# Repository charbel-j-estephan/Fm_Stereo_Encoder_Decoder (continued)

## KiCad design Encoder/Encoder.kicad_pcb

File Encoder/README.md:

# FM Stereo Encoder

## Final version

The final version is Encoder. Open Encoder.kicad_pro in KiCad 10. It holds the schematic (Encoder.kicad_sch) and the board (Encoder.kicad_pcb). Use these two files for printing and for building.

## Goal of this part

This board is the encoder half of the FM stereo project. It takes the left and right audio from the J3 input and turns them into one stereo multiplex (MPX) signal on the J4 output. The output feeds the FM transmitter module.

The board does these jobs.

1. It protects the inputs and filters the audio to 15 kHz.
2. It builds the sum (left plus right) and the difference (left minus right).
3. It makes a 38 kHz carrier. A CD4046 phase locked loop locks to a 19 kHz sine you feed into the 2 pin screw terminal (J5) and doubles it.
4. It modulates the difference signal onto the 38 kHz carrier with an MC1496.
5. It adds the sum, the modulated difference and the 19 kHz pilot into one MPX signal and filters it.

JP1 flips the carrier phase. If left and right come out swapped at the receiver, move the JP1 shunt to the other position. No reprint is needed.

## Board rules

- Tracks are 0.5 mm. The plus and minus 9 V rails use 0.8 mm tracks.
- Vias are 1.6 mm with a 0.8 mm drill. This is the board sent to PCBWay on Oct 24 (the "bigger vias" Gerbers).
- The four corner holes are 3.2 mm for M3 screws.
- Test points are single male header pins with 2.54 mm pitch. Break them off a 40 pin strip.
- The board is about 149 by 150 mm.

## Other files in this folder

- FM_Encoder_Build_and_Test_Guide.pdf is the stage by stage soldering and test guide. Follow it in order.
- FM_Encoder_Buy_List.xlsx is the EKT buy list with links and prices.
- MC1496.kicad_sym and R0.kicad_sym are symbol libraries the project needs. Do not delete them.

## Known open points

- J5 is a 2 pin 5.08 mm screw terminal. Pin 1 is the signal and pin 2 is ground. Feed it from a female BNC screw junction (EKT 426959) fixed to a bracket beside the board. The center screw goes to pin 1 and the shield screw goes to pin 2. No BNC part sits on the board.
- R51 (12k) and C47 (1n) set the VCO range. Check the free running frequency on TP33 during stage 7 of the guide.
- EKT does not stock 360k, 2.4k and 1.2n. The guide shows the substitutes.

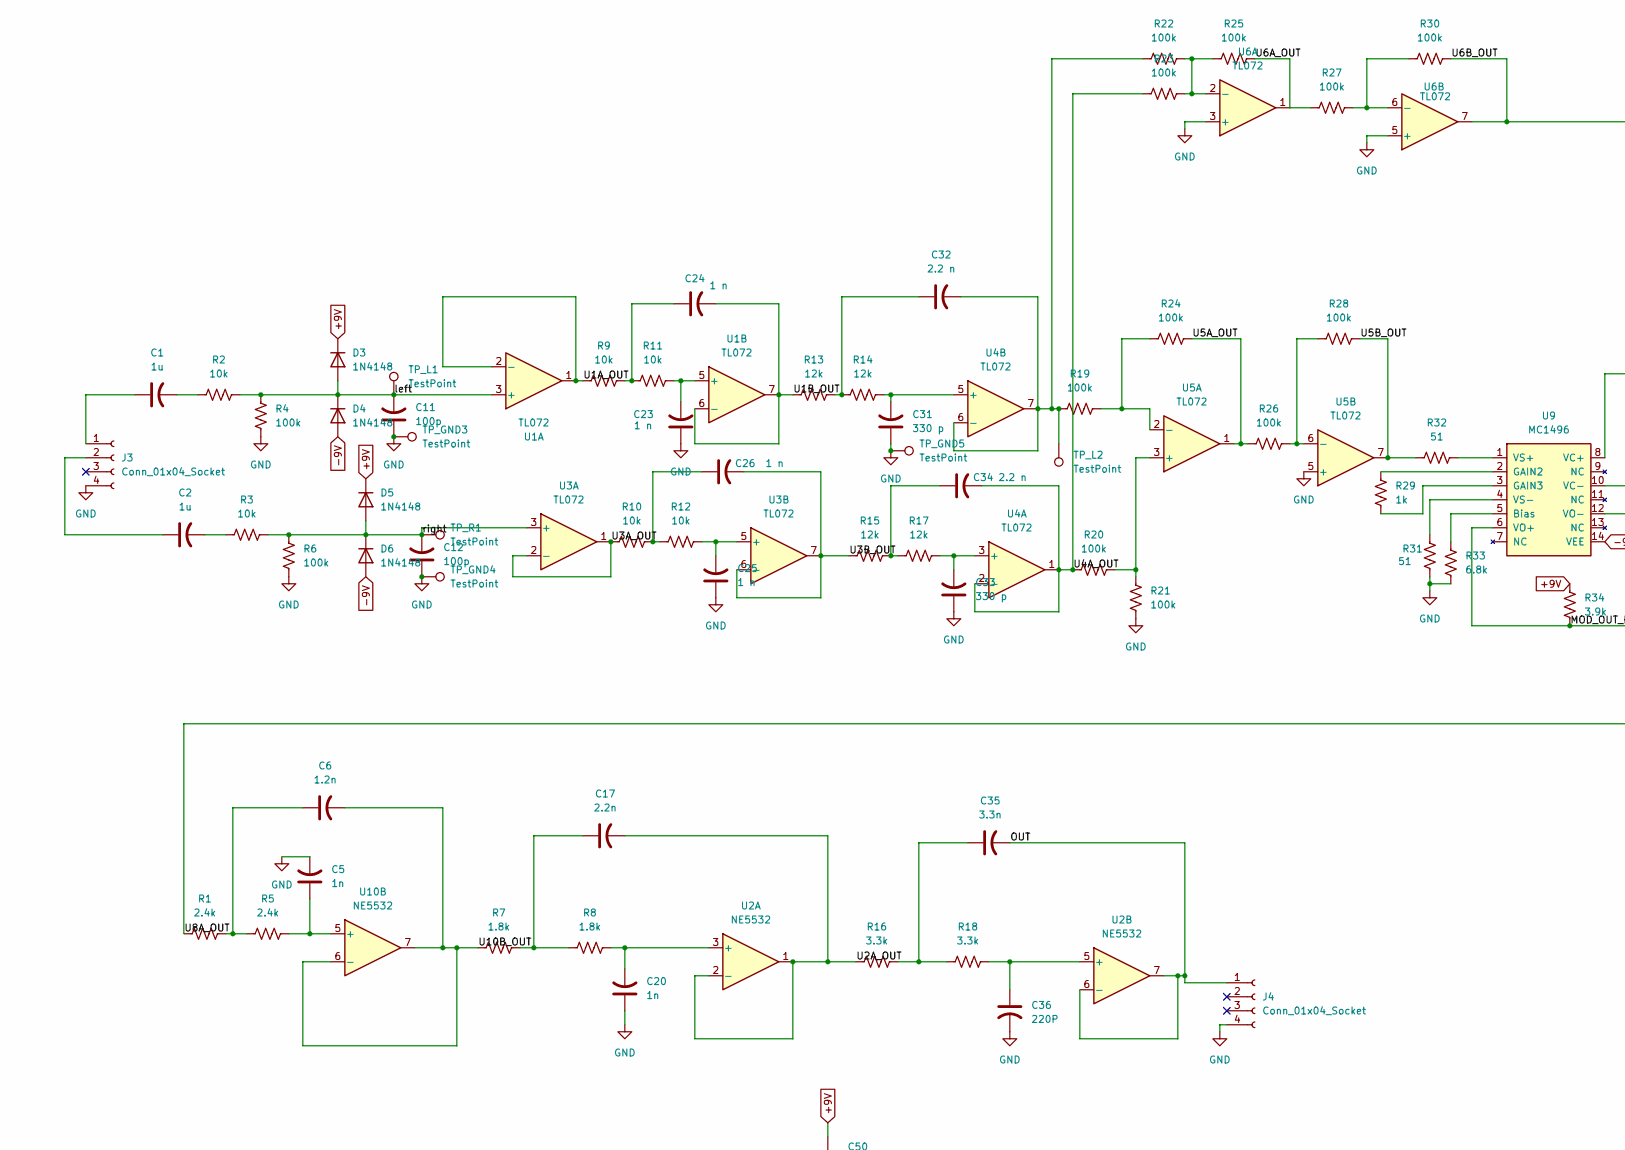
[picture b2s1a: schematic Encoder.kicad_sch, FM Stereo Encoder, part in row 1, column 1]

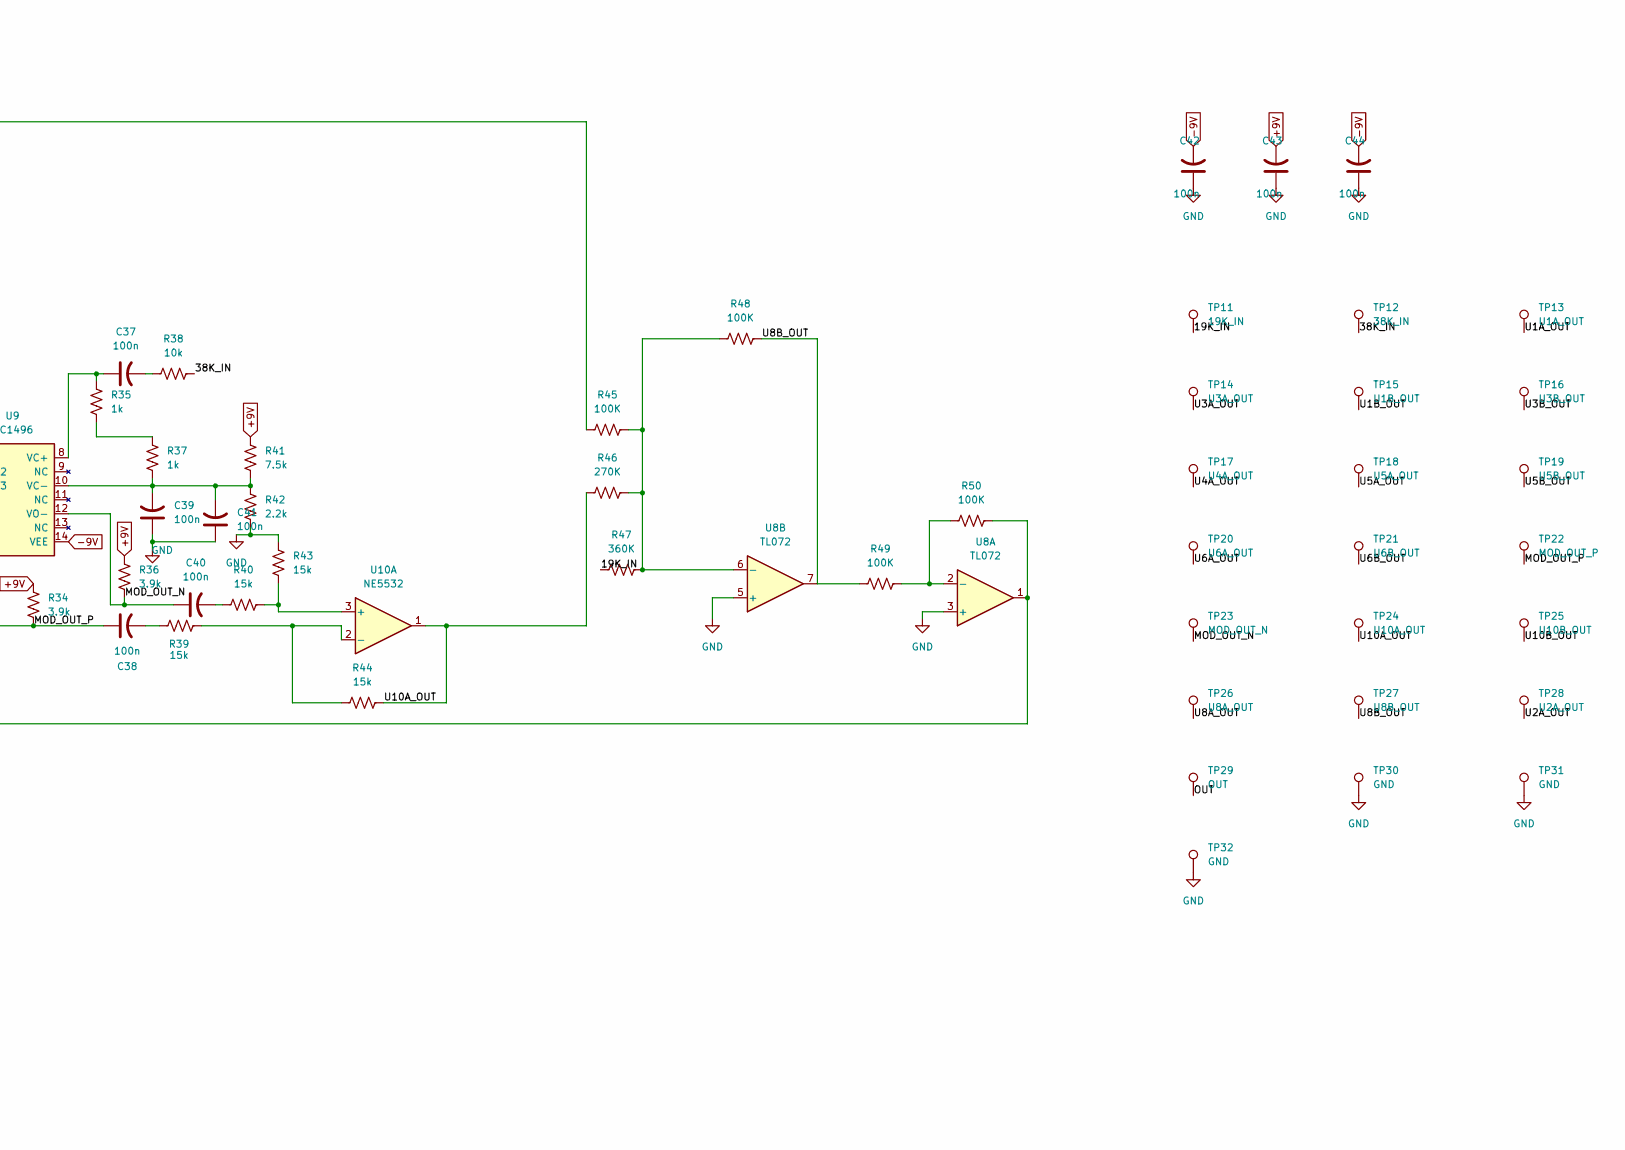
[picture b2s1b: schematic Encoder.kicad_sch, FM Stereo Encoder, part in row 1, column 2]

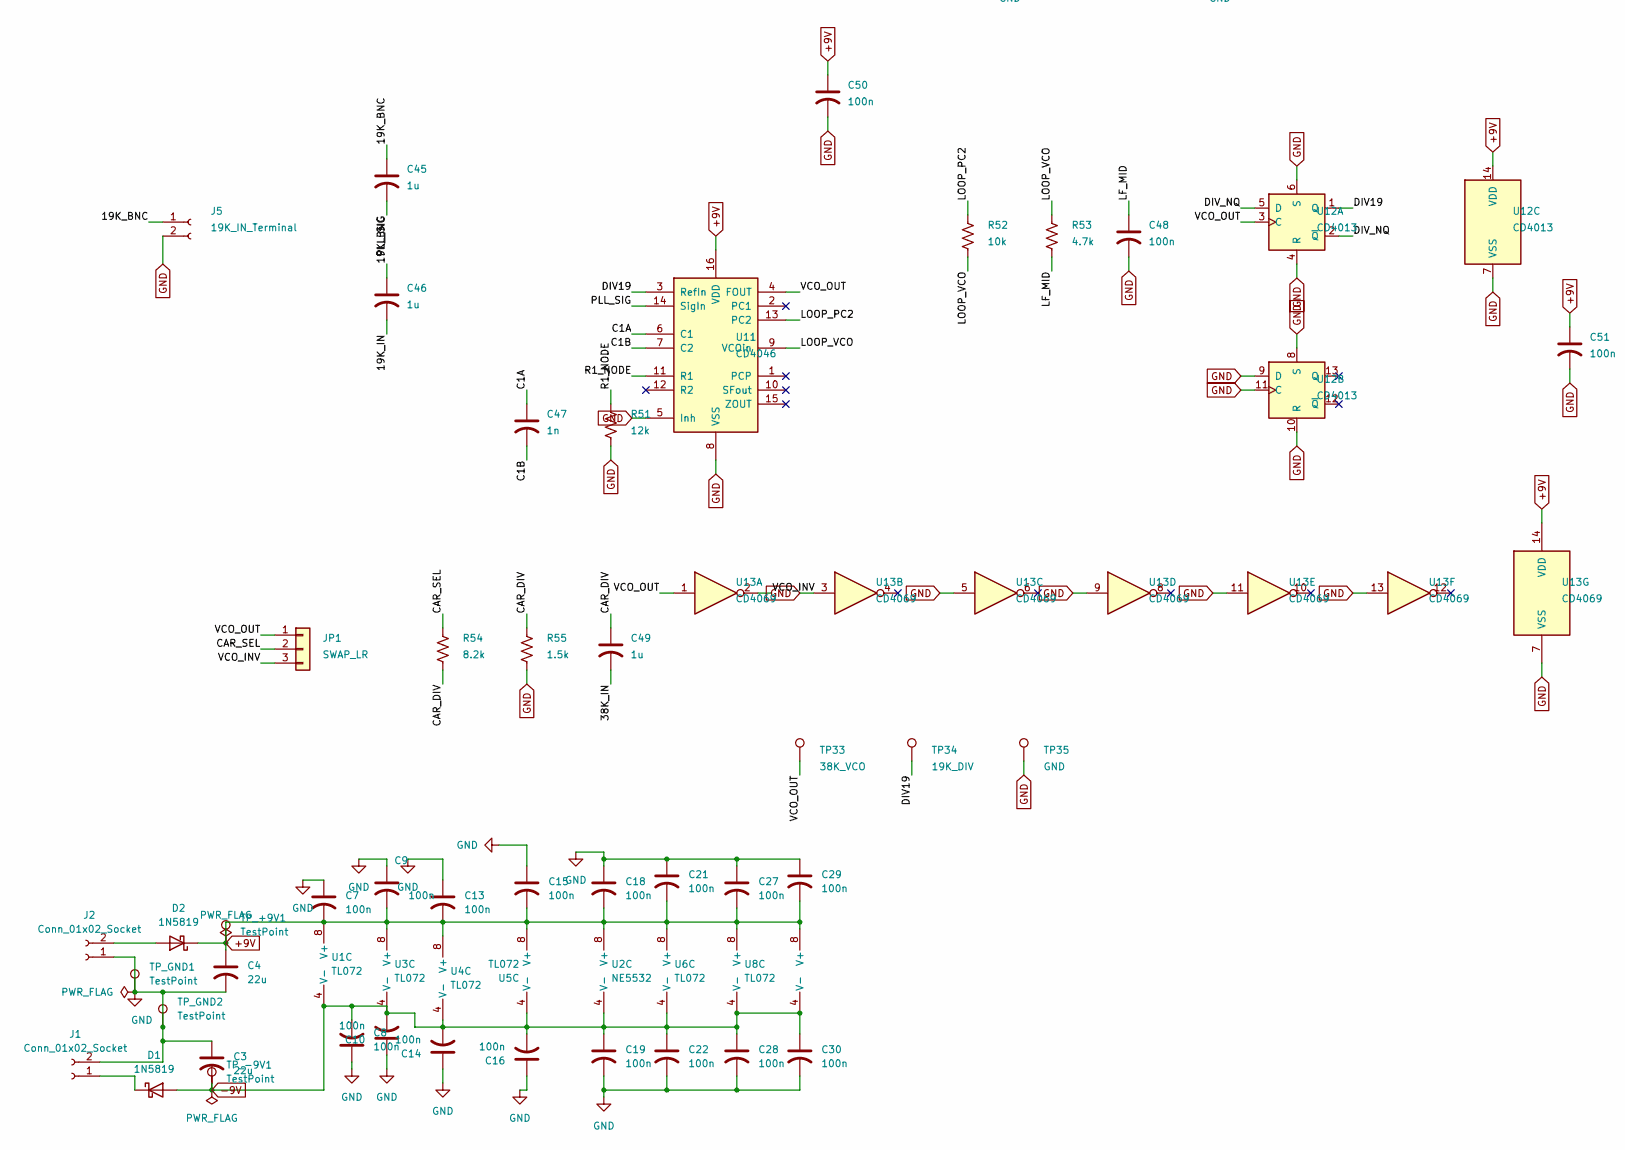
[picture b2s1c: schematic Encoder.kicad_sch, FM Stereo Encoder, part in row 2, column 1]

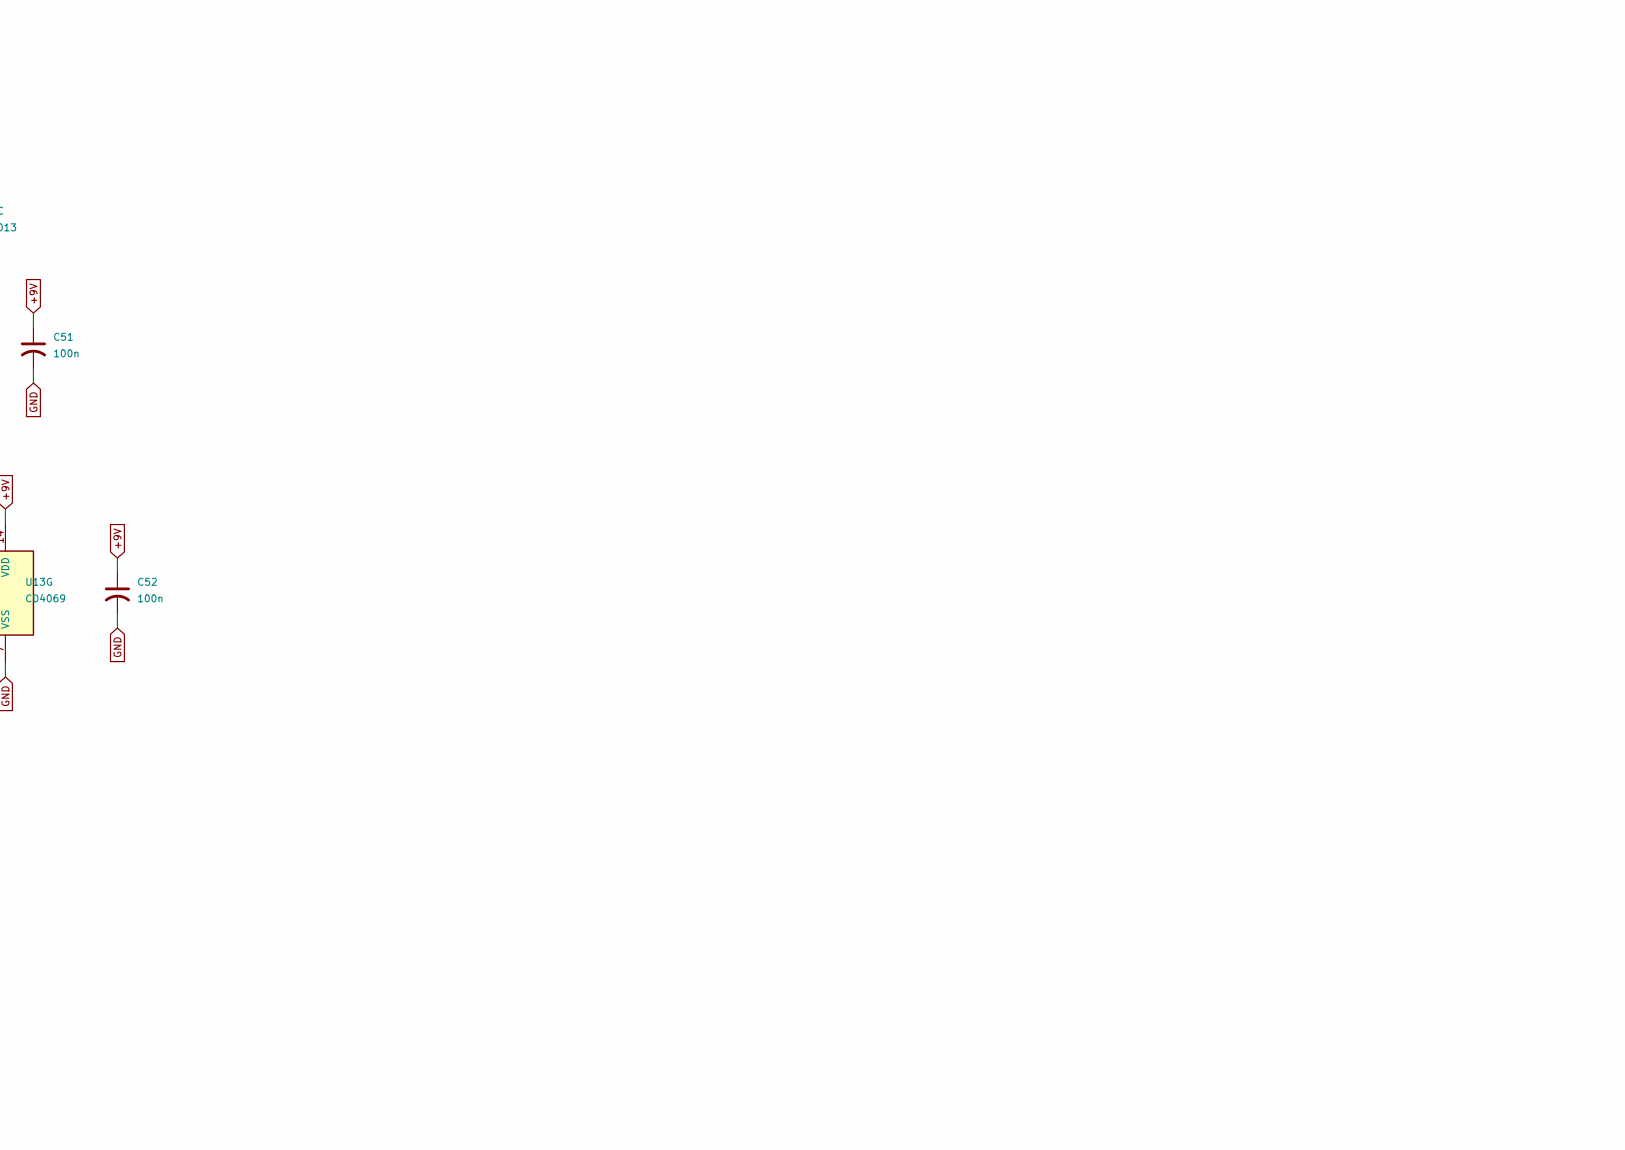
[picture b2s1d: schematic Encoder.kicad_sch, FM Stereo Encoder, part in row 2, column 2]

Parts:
C1, C2, C45, C46, C49: 1u; C_Rect_L7.2mm_W3.5mm_P5.00mm
C3, C4: 22u; CP_Radial_D8.0mm_P3.50mm
C5, C20, C47: 1n; C_Disc_D5.0mm_W2.5mm_P5.00mm
C6: 1.2n; C_Disc_D5.0mm_W2.5mm_P5.00mm
C7, C8, C9, C10, C13, C14, C15, C16, C18, C19, C21, C22, C27, C28, C29, C30, C37, C38, C39, C40, C41, C42, C43, C44, C48, C50, C51, C52: 100n; C_Disc_D5.0mm_W2.5mm_P5.00mm
C11, C12: 100p; C_Disc_D3.0mm_W2.0mm_P2.50mm
C17: 2.2n; C_Disc_D5.0mm_W2.5mm_P5.00mm
C23, C24, C25, C26: 1 n; C_Disc_D5.0mm_W2.5mm_P5.00mm
C31, C33: 330 p; C_Disc_D5.0mm_W2.5mm_P5.00mm
C32, C34: 2.2 n; C_Disc_D5.0mm_W2.5mm_P5.00mm
C35: 3.3n; C_Disc_D5.0mm_W2.5mm_P5.00mm
C36: 220P; C_Disc_D5.0mm_W2.5mm_P5.00mm
D1, D2: 1N5819; D_DO-41_SOD81_P10.16mm_Horizontal
D3, D4, D5, D6: 1N4148; D_DO-35_SOD27_P7.62mm_Horizontal
J1, J2: Conn_01x02_Socket; TerminalBlock_Phoenix_MKDS-1,5-2-5.08_1x02_P5.08mm_Horizont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
J3, J4: Conn_01x04_Socket; PinSocket_1x04_P2.54mm_Vertical
J5: 19K_IN_Terminal; TerminalBlock_Phoenix_MKDS-1,5-2-5.08_1x02_P5.08mm_Horizont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
JP1: SWAP_LR; PinHeader_1x03_P2.54mm_Vertical
R1, R5: 2.4k; R_Axial_DIN0207_L6.3mm_D2.5mm_P10.16mm_Horizontal
R2, R3, R9, R10, R11, R12, R38, R52: 10k; R_Axial_DIN0207_L6.3mm_D2.5mm_P10.16mm_Horizontal
R4, R6, R19, R20, R21, R22, R23, R24, R25, R26, R27, R28, R30: 100k; R_Axial_DIN0207_L6.3mm_D2.5mm_P10.16mm_Horizontal
R7, R8: 1.8k; R_Axial_DIN0207_L6.3mm_D2.5mm_P10.16mm_Horizontal
R13, R14, R15, R17, R51: 12k; R_Axial_DIN0207_L6.3mm_D2.5mm_P10.16mm_Horizontal
R16, R18: 3.3k; R_Axial_DIN0207_L6.3mm_D2.5mm_P10.16mm_Horizontal
R29, R35, R37: 1k; R_Axial_DIN0207_L6.3mm_D2.5mm_P10.16mm_Horizontal
R31, R32: 51; R_Axial_DIN0207_L6.3mm_D2.5mm_P10.16mm_Horizontal
R33: 6.8k; R_Axial_DIN0207_L6.3mm_D2.5mm_P10.16mm_Horizontal
R34, R36: 3.9k; R_Axial_DIN0207_L6.3mm_D2.5mm_P10.16mm_Horizontal
R39, R40, R43, R44: 15k; R_Axial_DIN0207_L6.3mm_D2.5mm_P10.16mm_Horizontal
R41: 7.5k; R_Axial_DIN0207_L6.3mm_D2.5mm_P10.16mm_Horizontal
R42: 2.2k; R_Axial_DIN0207_L6.3mm_D2.5mm_P10.16mm_Horizontal
R45, R48, R49, R50: 100K; R_Axial_DIN0207_L6.3mm_D2.5mm_P10.16mm_Horizontal
R46: 270K; R_Axial_DIN0207_L6.3mm_D2.5mm_P10.16mm_Horizontal
R47: 360K; R_Axial_DIN0207_L6.3mm_D2.5mm_P10.16mm_Horizontal
R53: 4.7k; R_Axial_DIN0207_L6.3mm_D2.5mm_P10.16mm_Horizontal
R54: 8.2k; R_Axial_DIN0207_L6.3mm_D2.5mm_P10.16mm_Horizontal
R55: 1.5k; R_Axial_DIN0207_L6.3mm_D2.5mm_P10.16mm_Horizontal
TP11: 19K_IN; PinHeader_1x01_P2.54mm_Vertical
TP12: 38K_IN; PinHeader_1x01_P2.54mm_Vertical
TP13: U1A_OUT; PinHeader_1x01_P2.54mm_Vertical
TP14: U3A_OUT; PinHeader_1x01_P2.54mm_Vertical
TP15: U1B_OUT; PinHeader_1x01_P2.54mm_Vertical
TP16: U3B_OUT; PinHeader_1x01_P2.54mm_Vertical
TP17: U4A_OUT; PinHeader_1x01_P2.54mm_Vertical
TP18: U5A_OUT; PinHeader_1x01_P2.54mm_Vertical
TP19: U5B_OUT; PinHeader_1x01_P2.54mm_Vertical
TP20: U6A_OUT; PinHeader_1x01_P2.54mm_Vertical
TP21: U6B_OUT; PinHeader_1x01_P2.54mm_Vertical
TP22: MOD_OUT_P; PinHeader_1x01_P2.54mm_Vertical
TP23: MOD_OUT_N; PinHeader_1x01_P2.54mm_Vertical
TP24: U10A_OUT; PinHeader_1x01_P2.54mm_Vertical
TP25: U10B_OUT; PinHeader_1x01_P2.54mm_Vertical
TP26: U8A_OUT; PinHeader_1x01_P2.54mm_Vertical
TP27: U8B_OUT; PinHeader_1x01_P2.54mm_Vertical
TP28: U2A_OUT; PinHeader_1x01_P2.54mm_Vertical
TP29: OUT; PinHeader_1x01_P2.54mm_Vertical
TP30, TP31, TP32, TP35: GND; PinHeader_1x01_P2.54mm_Vertical
TP33: 38K_VCO; PinHeader_1x01_P2.54mm_Vertical
TP34: 19K_DIV; PinHeader_1x01_P2.54mm_Vertical
TP_+9V1: TestPoint; PinHeader_1x01_P2.54mm_Vertical
TP_-9V1: TestPoint; PinHeader_1x01_P2.54mm_Vertical
TP_GND1, TP_GND2, TP_GND3, TP_GND4, TP_GND5: TestPoint; PinHeader_1x01_P2.54mm_Vertical
TP_L1, TP_L2: TestPoint; PinHeader_1x01_P2.54mm_Vertical
TP_R1: TestPoint; PinHeader_1x01_P2.54mm_Vertical
U1, U3, U4, U5, U6, U8: TL072; DIP-8_W7.62mm_Socket
U2, U10: NE5532; DIP-8_W7.62mm_Socket
U9: MC1496; DIP-14_W7.62mm_Socket
U11: CD4046; DIP-16_W7.62mm_Socket
U12: CD4013; DIP-14_W7.62mm_Socket
U13: CD4069; DIP-14_W7.62mm_Socket

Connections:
+9V: C4.1, C7.2, C9.2, C13.2, C15.2, C18.2, C21.2, C27.2, C29.2, C43.2, C50.1, C51.1, C52.1, D2.1 (K), D3.1 (K), D5.1 (K), R34.1, R36.1, R41.1, TP_+9V1.1, U1.8 (V+), U2.8 (V+), U3.8 (V+), U4.8 (V+), U5.8 (V+), U6.8 (V+), U8.8 (V+), U10.8 (V+), U11.16 (VDD), U12.14 (VDD), U13.14 (VDD)
-9V: C3.2, C8.2, C10.2, C14.2, C16.2, C19.1, C22.1, C28.1, C30.1, C42.2, C44.2, D1.2 (A), D4.2 (A), D6.2 (A), TP_-9V1.1, U1.4 (V-), U2.4 (V-), U3.4 (V-), U4.4 (V-), U5.4 (V-), U6.4 (V-), U8.4 (V-), U9.14 (VEE), U10.4 (V-)
/19K_BNC: C45.1, C46.1, J5.1
/19K_IN: C46.2, R47.1, TP11.1
/38K_IN: C49.2, R38.2, TP12.1
/C1A: C47.1, U11.6 (C1)
/C1B: C47.2, U11.7 (C2)
/CAR_DIV: C49.1, R54.2, R55.1
/CAR_SEL: JP1.2, R54.1
/DIV19: TP34.1, U11.3 (RefIn), U12.1 (Q)
/DIV_NQ: U12.2 (~Q), U12.5 (D)
/LF_MID: C48.1, R53.2
/LOOP_PC2: R52.1, U11.13 (PC2)
/LOOP_VCO: R52.2, R53.1, U11.9 (VCOin)
/MOD_OUT_N: C40.1, R36.2, TP23.1, U9.12 (VO-)
/MOD_OUT_P: C38.1, R34.2, TP22.1, U9.6 (VO+)
/OUT: C35.2, J4.1, TP29.1, U2.6 (-), U2.7
/PLL_SIG: C45.2, U11.14 (SigIn)
/R1_NODE: R51.1, U11.11 (R1)
/U1A_OUT: R9.1, TP13.1, U1.1, U1.2 (-)
/U1B_OUT: C24.2, R13.1, TP15.1, U1.6 (-), U1.7
/U2A_OUT: C17.2, R16.1, TP28.1, U2.1, U2.2 (-)
/U3A_OUT: R10.1, TP14.1, U3.1, U3.2 (-)
/U3B_OUT: C26.2, R15.1, TP16.1, U3.6 (-), U3.7
/U4A_OUT: C34.2, R20.1, R23.1, TP17.1, U4.1, U4.2 (-)
/U5A_OUT: R24.2, R26.1, TP18.1, U5.1
/U5B_OUT: R28.2, R32.1, TP19.1, U5.7
/U6A_OUT: R25.2, R27.1, TP20.1, U6.1
/U6B_OUT: R30.2, R45.1, TP21.1, U6.7
/U8A_OUT: R1.1, R50.2, TP26.1, U8.1
/U8B_OUT: R48.2, R49.1, TP27.1, U8.7
/U10A_OUT: R44.2, R46.1, TP24.1, U10.1
/U10B_OUT: C6.2, R7.1, TP25.1, U10.6 (-), U10.7
/VCO_INV: JP1.3, U13.2
/VCO_OUT: JP1.1, TP33.1, U11.4 (FOUT), U12.3 (C), U13.1
/left: C11.2, D3.2 (A), D4.1 (K), R2.2, R4.1, TP_L1.1, U1.3 (+)
/right: C12.2, D5.2 (A), D6.1 (K), R3.2, R6.1, TP_R1.1, U3.3 (+)
GND: C3.1, C4.2, C5.2, C7.1, C8.1, C9.1, C10.1, C11.1, C12.1, C13.1, C14.1, C15.1, C16.1, C18.1, C19.2, C20.1, C21.1, C22.2, C23.1, C25.1, C27.1, C28.2, C29.1, C30.2, C31.1, C33.1, C36.2, C39.1, C41.1, C42.1, C43.1, C44.1, C48.2, C50.2, C51.2, C52.2, J1.2, J2.1, J3.4, J4.4, J5.2, R4.2, R6.2, R21.2, R31.2, R33.2, R42.2, R43.1, R51.2, R55.2, TP30.1, TP31.1, TP32.1, TP35.1, TP_GND1.1, TP_GND2.1, TP_GND3.1, TP_GND4.1, TP_GND5.1, U5.5 (+), U6.3 (+), U6.5 (+), U8.3 (+), U8.5 (+), U11.5 (Inh), U11.8 (VSS), U12.4 (R), U12.6 (S), U12.7 (VSS), U12.8 (S), U12.9 (D), U12.10 (R), U12.11 (C), U13.3, U13.5, U13.7 (VSS), U13.9, U13.11, U13.13
unnamed: C1.2, R2.1
unnamed: C2.2, R3.1
unnamed: C6.1, R1.2, R5.1
unnamed: C17.1, R7.2, R8.1
unnamed: C24.1, R9.2, R11.1
unnamed: C26.1, R10.2, R12.1
unnamed: C32.1, R13.2, R14.1
unnamed: C34.1, R15.2, R17.1
unnamed: C35.1, R16.2, R18.1
unnamed: C37.2, R38.1
unnamed: C38.2, R39.2
unnamed: C40.2, R40.1
unnamed: D1.1 (K), J1.1
unnamed: D2.2 (A), J2.2
unnamed: C1.1, J3.1
unnamed: C2.1, J3.2
unnamed: R35.2, R37.1
unnamed: C23.2, R11.2, U1.5 (+)
unnamed: C20.2, R8.2, U2.3 (+)
unnamed: C36.1, R18.2, U2.5 (+)
unnamed: C25.2, R12.2, U3.5 (+)
unnamed: C33.2, R17.2, U4.3 (+)
unnamed: C31.2, R14.2, U4.5 (+)
unnamed: C32.2, R19.1, R22.1, TP_L2.1, U4.6 (-), U4.7
unnamed: R20.2, R21.1, U5.3 (+)
unnamed: R19.2, R24.1, U5.2 (-)
unnamed: R26.2, R28.1, U5.6 (-)
unnamed: R22.2, R23.2, R25.1, U6.2 (-)
unnamed: R27.2, R30.1, U6.6 (-)
unnamed: R49.2, R50.1, U8.2 (-)
unnamed: R45.2, R46.2, R47.2, R48.1, U8.6 (-)
unnamed: R33.1, U9.5 (Bias)
unnamed: R29.1, U9.2 (GAIN2)
unnamed: R29.2, U9.3 (GAIN3)
unnamed: C37.1, R35.1, U9.8 (VC+)
unnamed: C39.2, C41.2, R37.2, R41.2, R42.1, U9.10 (VC-)
unnamed: R32.2, U9.1 (VS+)
unnamed: R31.1, U9.4 (VS-)
unnamed: R40.2, R43.2, U10.3 (+)
unnamed: R39.1, R44.1, U10.2 (-)
unnamed: C5.1, R5.2, U10.5 (+)

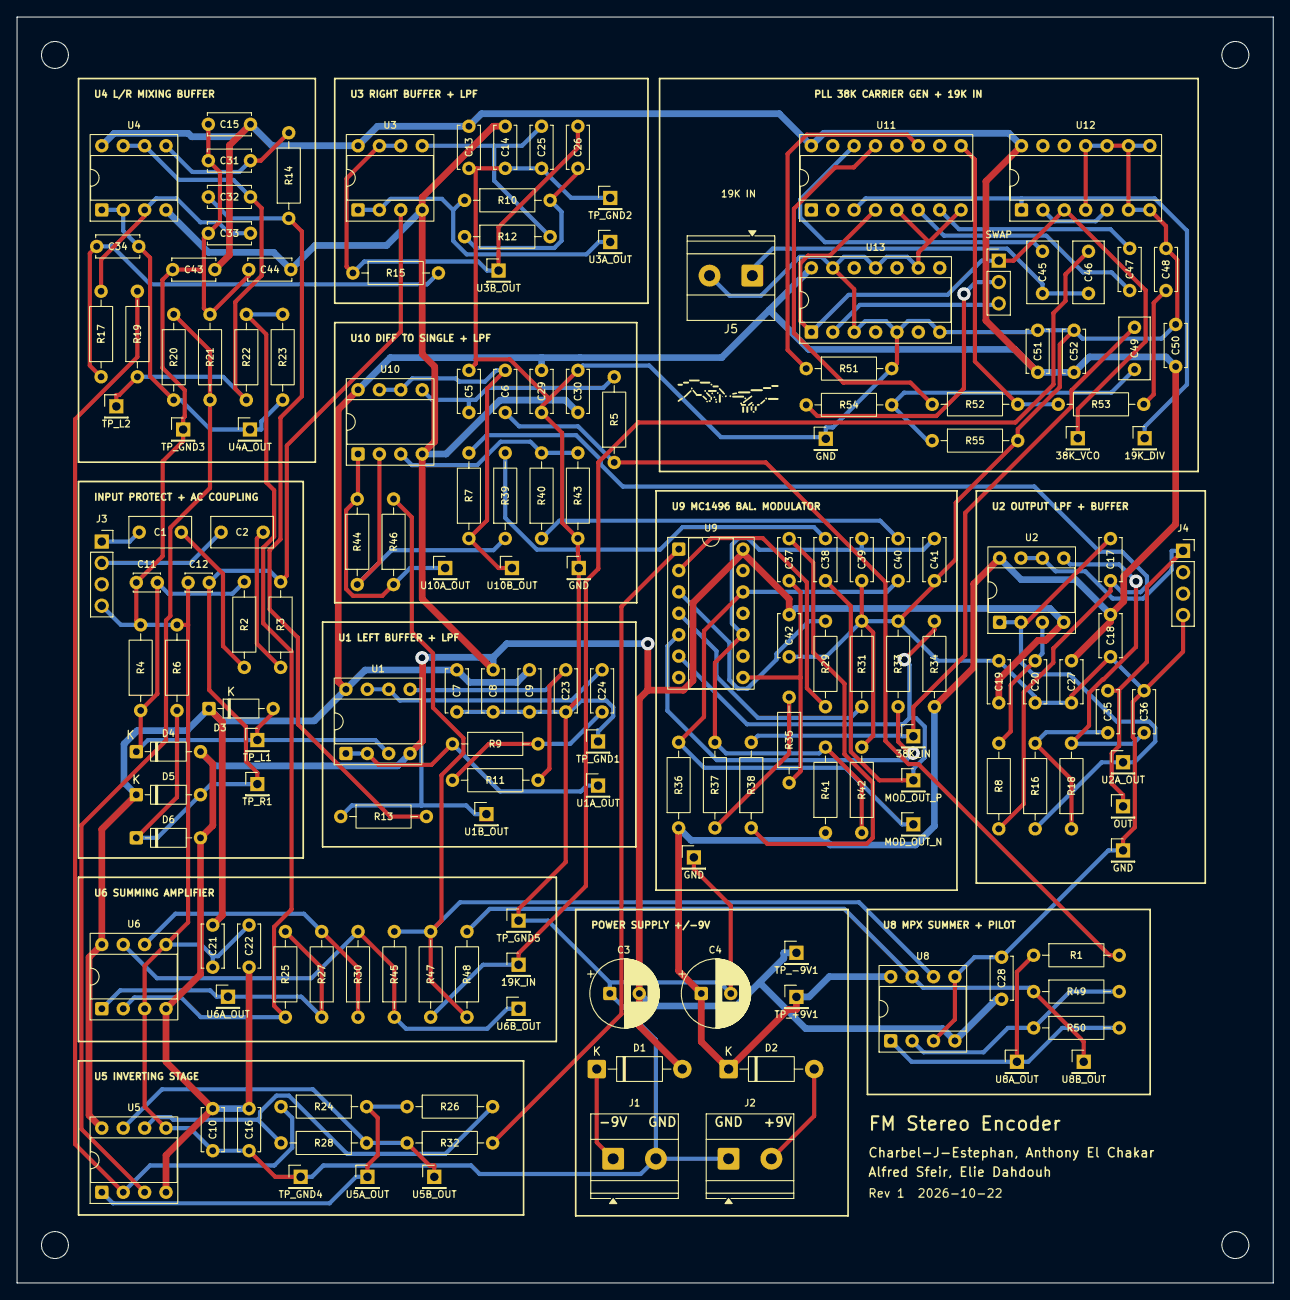
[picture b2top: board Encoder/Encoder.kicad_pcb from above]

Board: 2 copper layers, 149.1 x 150.3 mm, 170 parts (0 on the bottom side), 79 nets.

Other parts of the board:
H1, H2, H3, H4: M3; MountingHole_3.2mm_M3

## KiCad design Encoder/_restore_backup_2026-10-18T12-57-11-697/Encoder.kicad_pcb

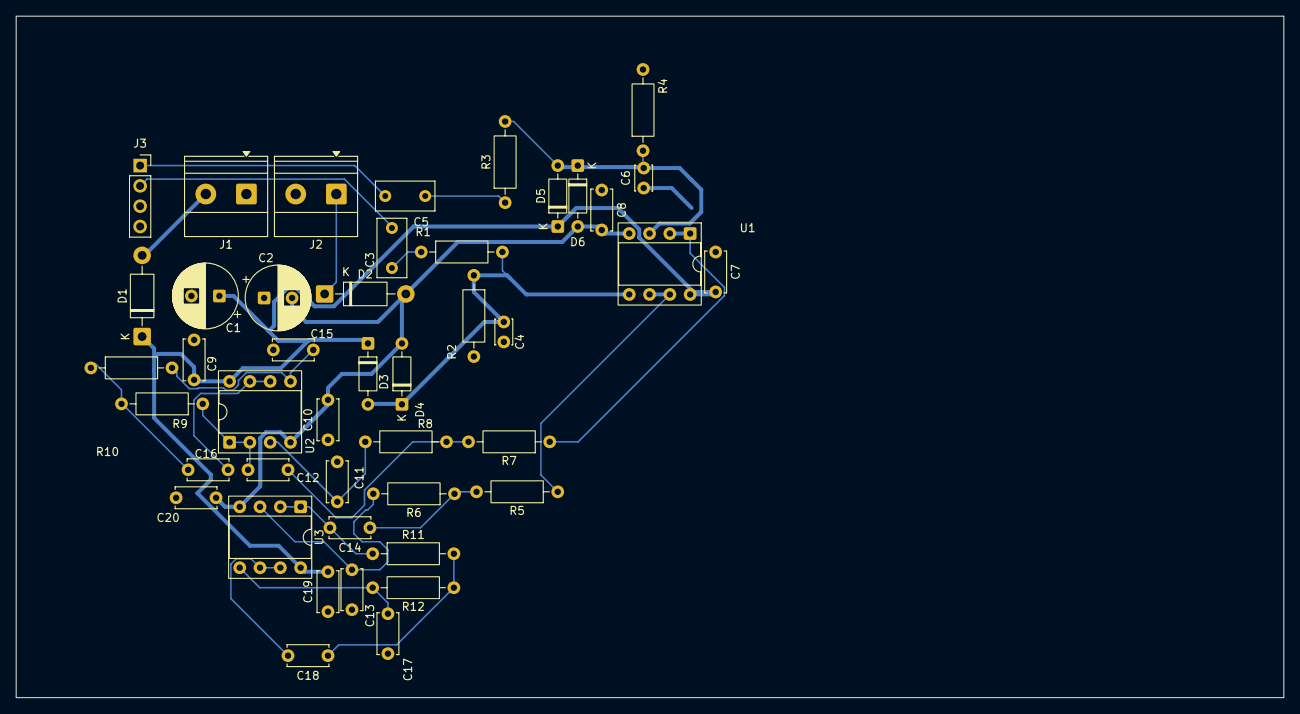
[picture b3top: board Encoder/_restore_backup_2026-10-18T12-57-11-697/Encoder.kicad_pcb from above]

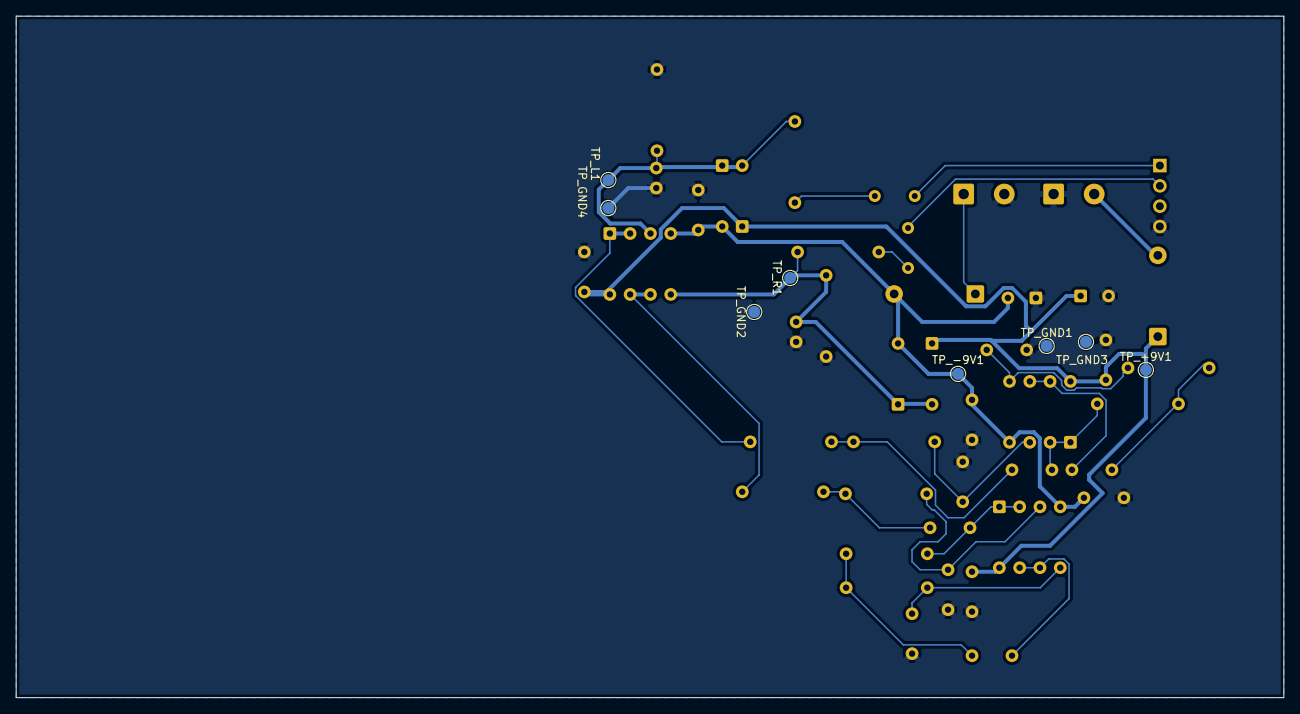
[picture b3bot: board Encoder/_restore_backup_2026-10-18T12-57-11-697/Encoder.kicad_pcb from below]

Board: 2 copper layers, 158.6 x 85.2 mm, 52 parts (8 on the bottom side), 25 nets.

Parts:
C1, C2: 22u; CP_Radial_D8.0mm_P3.50mm
C3, C5: 1u; C_Rect_L7.2mm_W3.5mm_P5.00mm
C4, C6: 100p; C_Disc_D3.0mm_W2.0mm_P2.50mm
C7, C8, C9, C10, C19, C20: 100n; C_Disc_D5.0mm_W2.5mm_P5.00mm
C11, C12, C13, C14: 1 n; C_Disc_D5.0mm_W2.5mm_P5.00mm
C15, C17: 330 p; C_Disc_D5.0mm_W2.5mm_P5.00mm
C16, C18: 2.2 n; C_Disc_D5.0mm_W2.5mm_P5.00mm
D1, D2: 1N5819; D_DO-41_SOD81_P10.16mm_Horizontal
D3, D4, D5, D6: 1N4148; D_DO-35_SOD27_P7.62mm_Horizontal
J1, J2: Conn_01x02_Socket; TerminalBlock_Phoenix_MKDS-1,5-2-5.08_1x02_P5.08mm_Horizont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
J3: Conn_01x04_Socket; PinSocket_1x04_P2.54mm_Vertical
R1, R3, R5, R6, R7, R8: 10k; R_Axial_DIN0207_L6.3mm_D2.5mm_P10.16mm_Horizontal
R2, R4: 100k; R_Axial_DIN0207_L6.3mm_D2.5mm_P10.16mm_Horizontal
R9, R10, R11, R12: 12k; R_Axial_DIN0207_L6.3mm_D2.5mm_P10.16mm_Horizontal
TP_+9V1: TestPoint; TestPoint_Pad_D1.5mm
TP_-9V1: TestPoint; TestPoint_Pad_D1.5mm
TP_GND1, TP_GND2, TP_GND3, TP_GND4: TestPoint; TestPoint_Pad_D1.5mm
TP_L1: TestPoint; TestPoint_Pad_D1.5mm
TP_R1: TestPoint; TestPoint_Pad_D1.5mm
U1, U2, U3: TL072; DIP-8_W7.62mm_Socket

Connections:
+9V: C1.1, C7.2, C9.2, C19.2, D1.1 (K), D3.1 (K), D5.1 (K), TP_+9V1.1 (1_1), U1.8 (V+), U2.8 (V+), U3.8 (V+)
-9V: C2.2, C8.2, C10.2, C20.2, D2.2 (A), D4.2 (A), D6.2 (A), TP_-9V1.1 (1_1), U1.4 (V-), U2.4 (V-), U3.4 (V-)
/left: C6.2, D5.2 (A), D6.1 (K), R3.2, R4.1, TP_L1.1 (1_1), U1.3 (+)
/right: C4.2, D3.2 (A), D4.1 (K), R1.2, R2.1, TP_R1.1 (1_1), U1.5 (+)
GND: C1.2, C2.1, C4.1, C6.1, C7.1, C8.1, C9.1, C10.1, C11.1, C13.1, C15.1, C17.1, C19.1, C20.1, J1.1, J2.2, J3.4, R2.2, R4.2, TP_GND1.1 (1_1), TP_GND2.1 (1_1), TP_GND3.1 (1_1), TP_GND4.1 (1_1)
unnamed: C3.2, R1.1
unnamed: C5.2, R3.1
unnamed: C12.1, R7.2, R8.1
unnamed: C14.1, R5.2, R6.1
unnamed: C16.1, R9.2, R10.1
unnamed: C18.1, R11.2, R12.1
unnamed: D1.2 (A), J1.2
unnamed: D2.1 (K), J2.1
unnamed: C5.1, J3.1
unnamed: C3.1, J3.2
unnamed: R7.1, U1.1, U1.2 (-)
unnamed: R5.1, U1.6 (-), U1.7
unnamed: C11.2, R8.2, U2.3 (+)
unnamed: C12.2, R9.1, U2.1, U2.2 (-)
unnamed: C15.2, R10.2, U2.5 (+)
unnamed: C16.2, U2.6 (-), U2.7
unnamed: C13.2, R6.2, U3.3 (+)
unnamed: C14.2, R11.1, U3.1, U3.2 (-)
unnamed: C17.2, R12.2, U3.5 (+)
unnamed: C18.2, U3.6 (-), U3.7

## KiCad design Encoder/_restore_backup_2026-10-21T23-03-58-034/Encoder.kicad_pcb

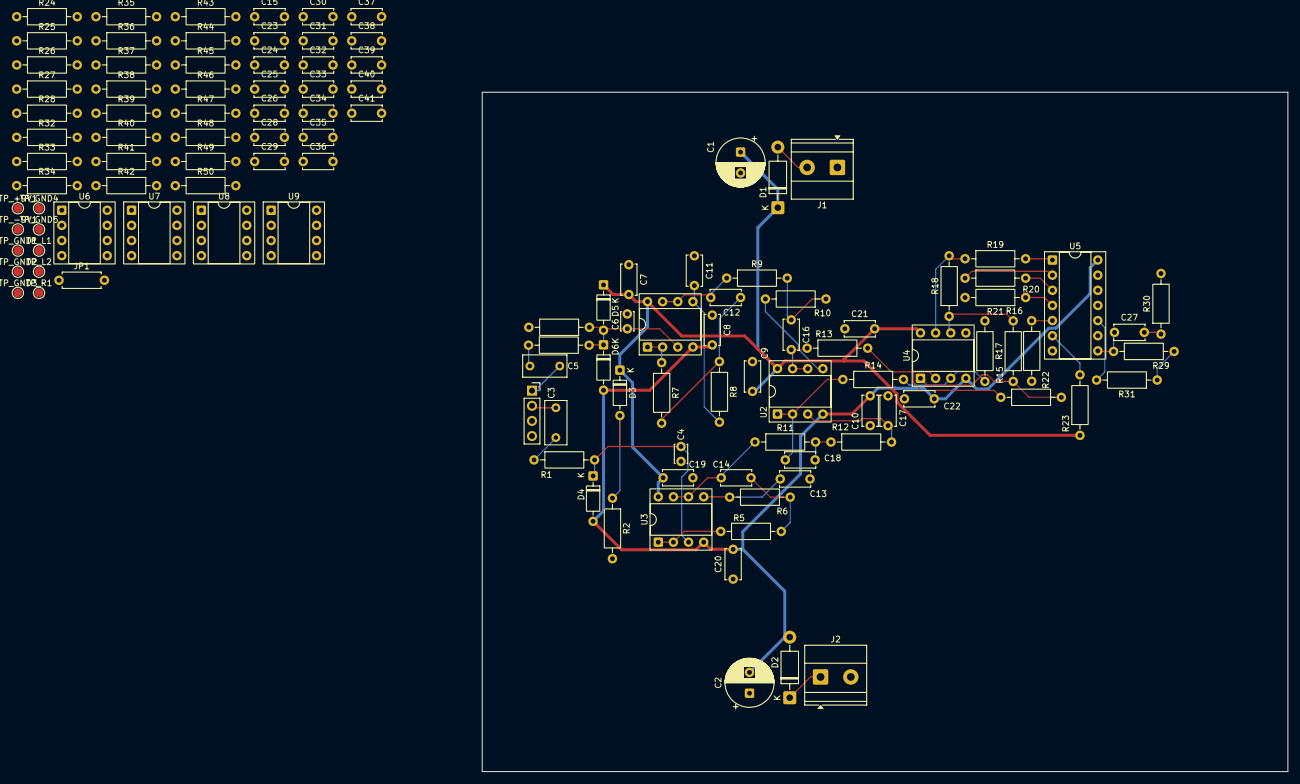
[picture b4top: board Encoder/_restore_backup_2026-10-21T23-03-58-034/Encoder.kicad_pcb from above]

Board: 2 copper layers, 135.2 x 114.0 mm, 120 parts (0 on the bottom side), 63 nets.

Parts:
C1, C2: 22u; CP_Radial_D8.0mm_P3.50mm
C3, C5: 1u; C_Rect_L7.2mm_W3.5mm_P5.00mm
C4, C6: 100p; C_Disc_D3.0mm_W2.0mm_P2.50mm
C7, C8, C9, C10, C19, C20, C21, C22, C23, C24, C25, C26, C27, C28, C29, C30, C31, C38, C39, C40, C41: 100n; C_Disc_D5.0mm_W2.5mm_P5.00mm
C11, C12, C13, C14: 1 n; C_Disc_D5.0mm_W2.5mm_P5.00mm
C15, C17: 330 p; C_Disc_D5.0mm_W2.5mm_P5.00mm
C16, C18: 2.2 n; C_Disc_D5.0mm_W2.5mm_P5.00mm
C32, C35: 1n; C_Disc_D5.0mm_W2.5mm_P5.00mm
C33: 1.2n; C_Disc_D5.0mm_W2.5mm_P5.00mm
C34: 2.2n; C_Disc_D5.0mm_W2.5mm_P5.00mm
C36: 3.3n; C_Disc_D5.0mm_W2.5mm_P5.00mm
C37: 220P; C_Disc_D5.0mm_W2.5mm_P5.00mm
D1, D2: 1N5819; D_DO-41_SOD81_P10.16mm_Horizontal
D3, D4, D5, D6: 1N4148; D_DO-35_SOD27_P7.62mm_Horizontal
J1, J2: Conn_01x02_Socket; TerminalBlock_Phoenix_MKDS-1,5-2-5.08_1x02_P5.08mm_Horizont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
J3: Conn_01x04_Socket; PinSocket_1x04_P2.54mm_Vertical
JP1: Jumper_0R; R_Axial_DIN0207_L6.3mm_D2.5mm_P7.62mm_Horizontal
R1, R3, R5, R6, R7, R8, R30: 10k; R_Axial_DIN0207_L6.3mm_D2.5mm_P10.16mm_Horizontal
R2, R4, R13, R14, R15, R16, R17, R18, R34, R35, R36, R37, R38: 100k; R_Axial_DIN0207_L6.3mm_D2.5mm_P10.16mm_Horizontal
R9, R10, R11, R12: 12k; R_Axial_DIN0207_L6.3mm_D2.5mm_P10.16mm_Horizontal
R19, R21: 51; R_Axial_DIN0207_L6.3mm_D2.5mm_P10.16mm_Horizontal
R20, R29, R31: 1k; R_Axial_DIN0207_L6.3mm_D2.5mm_P10.16mm_Horizontal
R22: 6.8k; R_Axial_DIN0207_L6.3mm_D2.5mm_P10.16mm_Horizontal
R23, R24: 3.9k; R_Axial_DIN0207_L6.3mm_D2.5mm_P10.16mm_Horizontal
R25, R26, R27, R28: 15k; R_Axial_DIN0207_L6.3mm_D2.5mm_P10.16mm_Horizontal
R32: 7.5k; R_Axial_DIN0207_L6.3mm_D2.5mm_P10.16mm_Horizontal
R33: 2.2k; R_Axial_DIN0207_L6.3mm_D2.5mm_P10.16mm_Horizontal
R39, R40: 2.4k; R_Axial_DIN0207_L6.3mm_D2.5mm_P10.16mm_Horizontal
R41, R42: 1.8k; R_Axial_DIN0207_L6.3mm_D2.5mm_P10.16mm_Horizontal
R43, R44: 3.3k; R_Axial_DIN0207_L6.3mm_D2.5mm_P10.16mm_Horizontal
R45, R48, R49, R50: 100K; R_Axial_DIN0207_L6.3mm_D2.5mm_P10.16mm_Horizontal
R46: 270K; R_Axial_DIN0207_L6.3mm_D2.5mm_P10.16mm_Horizontal
R47: 360K; R_Axial_DIN0207_L6.3mm_D2.5mm_P10.16mm_Horizontal
TP_+9V1: TestPoint; TestPoint_Pad_D1.5mm
TP_-9V1: TestPoint; TestPoint_Pad_D1.5mm
TP_GND1, TP_GND2, TP_GND3, TP_GND4, TP_GND5: TestPoint; TestPoint_Pad_D1.5mm
TP_L1, TP_L2: TestPoint; TestPoint_Pad_D1.5mm
TP_R1: TestPoint; TestPoint_Pad_D1.5mm
U1, U2, U3, U4, U7, U9: TL072; DIP-8_W7.62mm_Socket
U5: MC1496; DIP-14_W7.62mm_Socket
U6, U8: NE5532; DIP-8_W7.62mm_Socket

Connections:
+9V: C1.1, C7.2, C9.2, C19.2, C21.2, C26.2, C30.2, C38.2, C39.2, D1.1 (K), D3.1 (K), D5.1 (K), R23.1, R24.1, R32.1, TP_+9V1.1 (1_1), U1.8 (V+), U2.8 (V+), U3.8 (V+), U4.8 (V+), U6.8 (V+), U7.8 (V+), U8.8 (V+), U9.8 (V+)
-9V: C2.2, C8.2, C10.2, C20.2, C22.2, C25.1, C31.1, C40.1, C41.1, D2.2 (A), D4.2 (A), D6.2 (A), JP1.1 (A_1), TP_-9V1.1 (1_1), U1.4 (V-), U2.4 (V-), U3.4 (V-), U4.4 (V-), U5.14 (VEE), U6.4 (V-), U7.4 (V-), U8.4 (V-), U9.4 (V-)
/left: C6.2, D5.2 (A), D6.1 (K), R3.2, R4.1, TP_L1.1 (1_1), U1.3 (+)
/right: C4.2, D3.2 (A), D4.1 (K), R1.2, R2.1, TP_R1.1 (1_1), U3.3 (+)
GND: C1.2, C2.1, C4.1, C6.1, C7.1, C8.1, C9.1, C10.1, C11.1, C13.1, C15.1, C17.1, C19.1, C20.1, C21.1, C22.1, C25.2, C26.1, C28.1, C29.1, C30.1, C31.2, C32.2, C35.1, C37.2, C38.1, C39.1, C40.2, C41.2, J1.1, J2.2, J3.4, R2.2, R4.2, R15.2, R21.2, R22.2, R27.1, R33.2, TP_GND1.1 (1_1), TP_GND2.1 (1_1), TP_GND3.1 (1_1), TP_GND4.1 (1_1), TP_GND5.1 (1_1), U4.5 (+), U7.3 (+), U7.5 (+), U9.3 (+), U9.5 (+)
unnamed: C3.2, R1.1
unnamed: C5.2, R3.1
unnamed: C12.1, R7.2, R8.1
unnamed: C14.1, R5.2, R6.1
unnamed: C16.1, R9.2, R10.1
unnamed: C18.1, R11.2, R12.1
unnamed: C23.2, R25.1
unnamed: C24.2, R26.2
unnamed: C27.2, R30.1
unnamed: C33.1, R39.1, R40.2
unnamed: C34.1, R41.2, R42.1
unnamed: C36.1, R43.2, R44.1
unnamed: D1.2 (A), J1.2
unnamed: D2.1 (K), J2.1
unnamed: C5.1, J3.1
unnamed: C3.1, J3.2
unnamed: R16.2, R17.1, U4.1
unnamed: R18.2, R19.1, U4.7
unnamed: R28.2, R46.1, U6.1
unnamed: R29.2, R31.1
unnamed: R36.2, R37.1, U7.1
unnamed: R38.2, R45.1, U7.7
unnamed: R40.1, R50.2, U9.7
unnamed: R48.2, R49.1, U9.1
unnamed: R7.1, U1.1, U1.2 (-)
unnamed: C11.2, R8.2, U1.5 (+)
unnamed: C12.2, R9.1, U1.6 (-), U1.7
unnamed: C17.2, R12.2, U2.3 (+)
unnamed: C18.2, R14.1, R35.1, U2.1, U2.2 (-)
unnamed: C15.2, R10.2, U2.5 (+)
unnamed: C16.2, R13.1, R34.1, TP_L2.1 (1_1), U2.6 (-), U2.7
unnamed: R5.1, U3.1, U3.2 (-)
unnamed: C13.2, R6.2, U3.5 (+)
unnamed: C14.2, R11.1, U3.6 (-), U3.7
unnamed: R14.2, R15.1, U4.3 (+)
unnamed: R13.2, R16.1, U4.2 (-)
unnamed: R17.2, R18.1, U4.6 (-)
unnamed: R22.1, U5.5 (Bias)
unnamed: R20.1, U5.2 (GAIN2)
unnamed: R20.2, U5.3 (GAIN3)
unnamed: C27.1, R29.1, U5.8 (VC+)
unnamed: C28.2, C29.2, R31.2, R32.2, R33.1, U5.10 (VC-)
unnamed: C24.1, R23.2, U5.6 (VO+)
unnamed: C23.1, R24.2, U5.12 (VO-)
unnamed: R19.2, U5.1 (VS+)
unnamed: R21.1, U5.4 (VS-)
unnamed: R25.2, R27.2, U6.3 (+)
unnamed: R26.1, R28.1, U6.2 (-)
unnamed: C32.1, R39.2, U6.5 (+)
unnamed: C33.2, R41.1, U6.6 (-), U6.7
unnamed: R34.2, R35.2, R36.1, U7.2 (-)
unnamed: R37.2, R38.1, U7.6 (-)
unnamed: C34.2, R43.1, U8.1, U8.3 (+)
unnamed: C35.2, R42.2, U8.2 (-)
unnamed: C36.2, U8.5 (+), U8.7
unnamed: C37.1, R44.2, U8.6 (-)
unnamed: R45.2, R46.2, R47.2, R48.1, U9.2 (-)
unnamed: R49.2, R50.1, U9.6 (-)
